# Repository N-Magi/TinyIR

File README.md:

# TinyIR
Key Switch Size IR remote controller

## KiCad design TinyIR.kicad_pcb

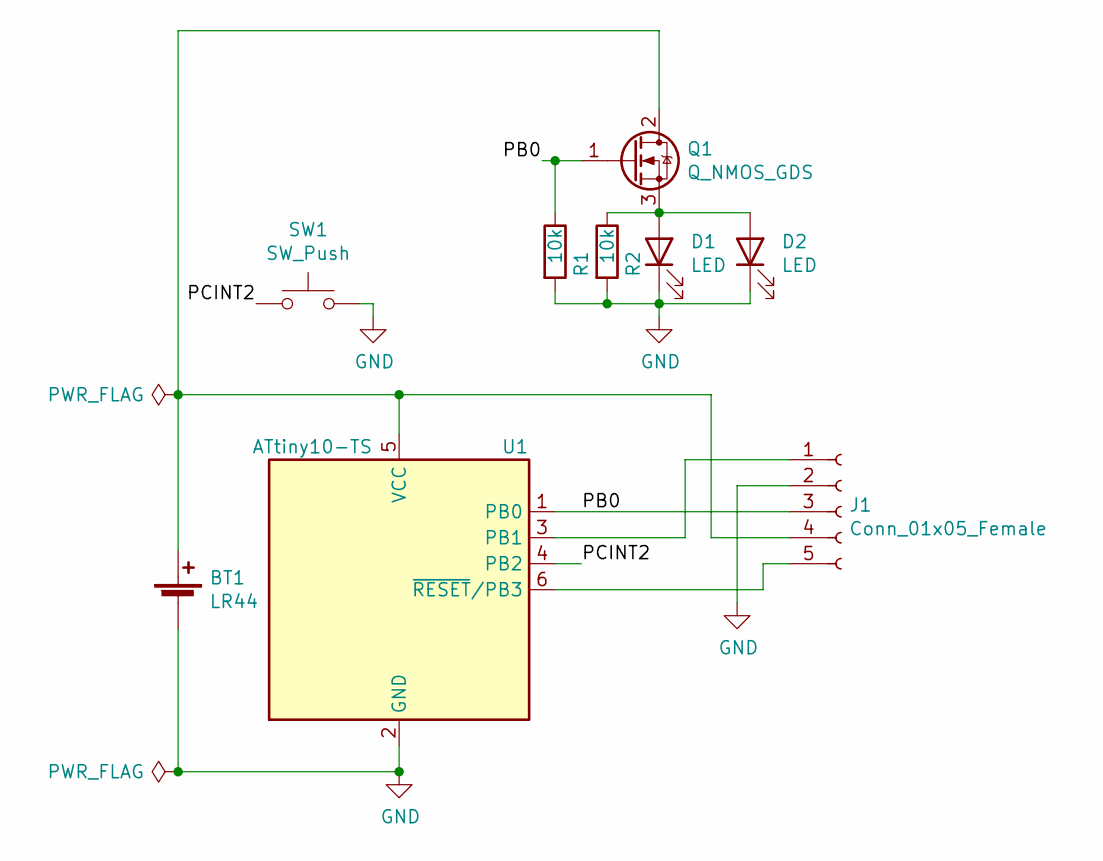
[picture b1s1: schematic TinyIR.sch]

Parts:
BT1: LR44; PinHeader_2x01_P1.00mm_Vertical_SMD
D1, D2: LED; LED_PLCC_2835_Handsoldering
J1: Conn_01x05_Female; PinHeader_1x05_P1.27mm_Vertical
Q1: Q_NMOS_GDS; TSOT-23_HandSoldering
R1, R2: 10k; R_0805_2012Metric_Pad1.15x1.40mm_HandSolder
SW1: SW_Push; SW_Cherry_MX_1.00u_PCB
U1: ATtiny10-TS; SOT-23-6_Handsoldering

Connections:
/PB0: J1.3, Q1.1 (G), R1.1, U1.1 (PB0)
/PCINT2: SW1.1, U1.4 (PB2)
GND: BT1.2 (-), D1.1 (K), D2.1 (K), J1.2, R1.2, R2.2, SW1.2, U1.2 (GND)
unnamed: BT1.1 (+), J1.4, Q1.2 (D), U1.5 (VCC)
unnamed: D1.2 (A), D2.2 (A), Q1.3 (S), R2.1
unnamed: J1.1, U1.3 (PB1)
unnamed: J1.5, U1.6 (~RESET~/PB3)

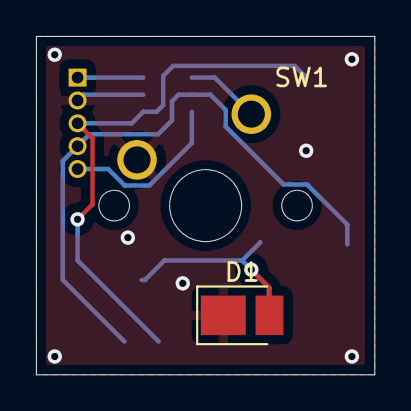
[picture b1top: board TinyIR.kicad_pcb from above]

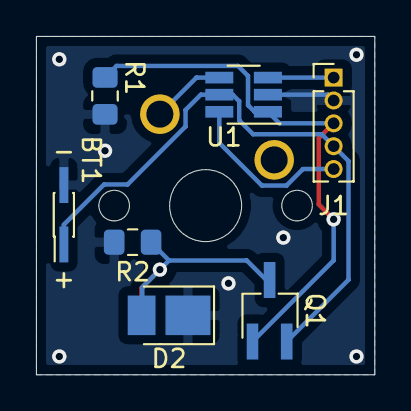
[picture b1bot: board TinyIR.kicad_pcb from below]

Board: 2 copper layers, 18.8 x 18.8 mm, 9 parts (7 on the bottom side), 7 nets.
